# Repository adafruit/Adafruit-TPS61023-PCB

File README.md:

## Adafruit Adafruit MiniBoost 5V at 1A - TPS61023 PCB

<a href="http://www.adafruit.com/products/4654"><br/>
Click here to purchase one from the Adafruit shop</a>

PCB files for the Adafruit Adafruit MiniBoost 5V at 1A - TPS61023.

Format is EagleCAD schematic and board layout
* https://www.adafruit.com/product/4654

### Description

This adorable little board will come in very handy whenever you need a good amount of 5V power. It's the size of a linear regulator, but it's actually a mini-booster! Input 2-5VDC on one side, and get 5V at up to 1A supply on the other. Perfect for use with battery-powered projects with 2 or 3 Alkaline, or a single Lithium battery.

This booster uses a very small but thermally efficient chip from TI, the TPS61023. This chip has nearly everything integrated, including dual 3A MOSFET switches. Note that the switch doesn't tell you the max output, see the tables below for that!

We set the feedback resistors to give a 5.2V output, this is a little higher than 5V which helps account for voltage drop over cables. We took some measurements of the input/output current and max draw using a bench-top power supply and electronic load:

    At 2V DC in, max current out at 5V is 300mA (the minimum input voltage that will 'boot' the booster)
    At 2.5V DC in, max current out at 5V is 500mA (two NiMH rechargables)
    At 3V DC in, max current out at 5V is 800mA (two alkalines or a near-dead LiPo)
    At 3.5V DC in, max current out at 5V is 1100 mA (this is a LiPoly nominal voltage)
    At 4V DC in, max current out at 5V is 1400 mA (3 NiMH, or a fresh LiPoly)

Most people will want to use a Lipoly or LiIon battery with a booster, with a nominal voltage of 3.7V. Here's the efficiencies at that voltage:

    5.2V 100mA out requires 160mA in at 3.7V (88%)
    5.2V 250mA out requires 400mA in at 3.7V (88%)
    5.2V 500mA out requires 800mA in at 3.7V (88%)
    5.2V 1000mA out requires 1800mA in at 3.7V (78%)

As you can see, you'll be humming at ~88% as 'lower' currents of about 500mA and less. You can get 1A out but your efficiency will drop a bit to ~78%

You get one fully assembled breakout with a TPS61023 and components, and a small bit of header. Give it 3-5V on the IN and ground pins. Then you'll have 5V on the OUT pin. The enable pin can be pulled low to disable the output, its a 'true disconnect' so the output will be completely de-powered.

### License

Adafruit invests time and resources providing this open source design, please support Adafruit and open-source hardware by purchasing products from [Adafruit](https://www.adafruit.com)!

Designed by Limor Fried/Ladyada for Adafruit Industries.

Creative Commons Attribution/Share-Alike, all text above must be included in any redistribution.
See license.txt for additional details.

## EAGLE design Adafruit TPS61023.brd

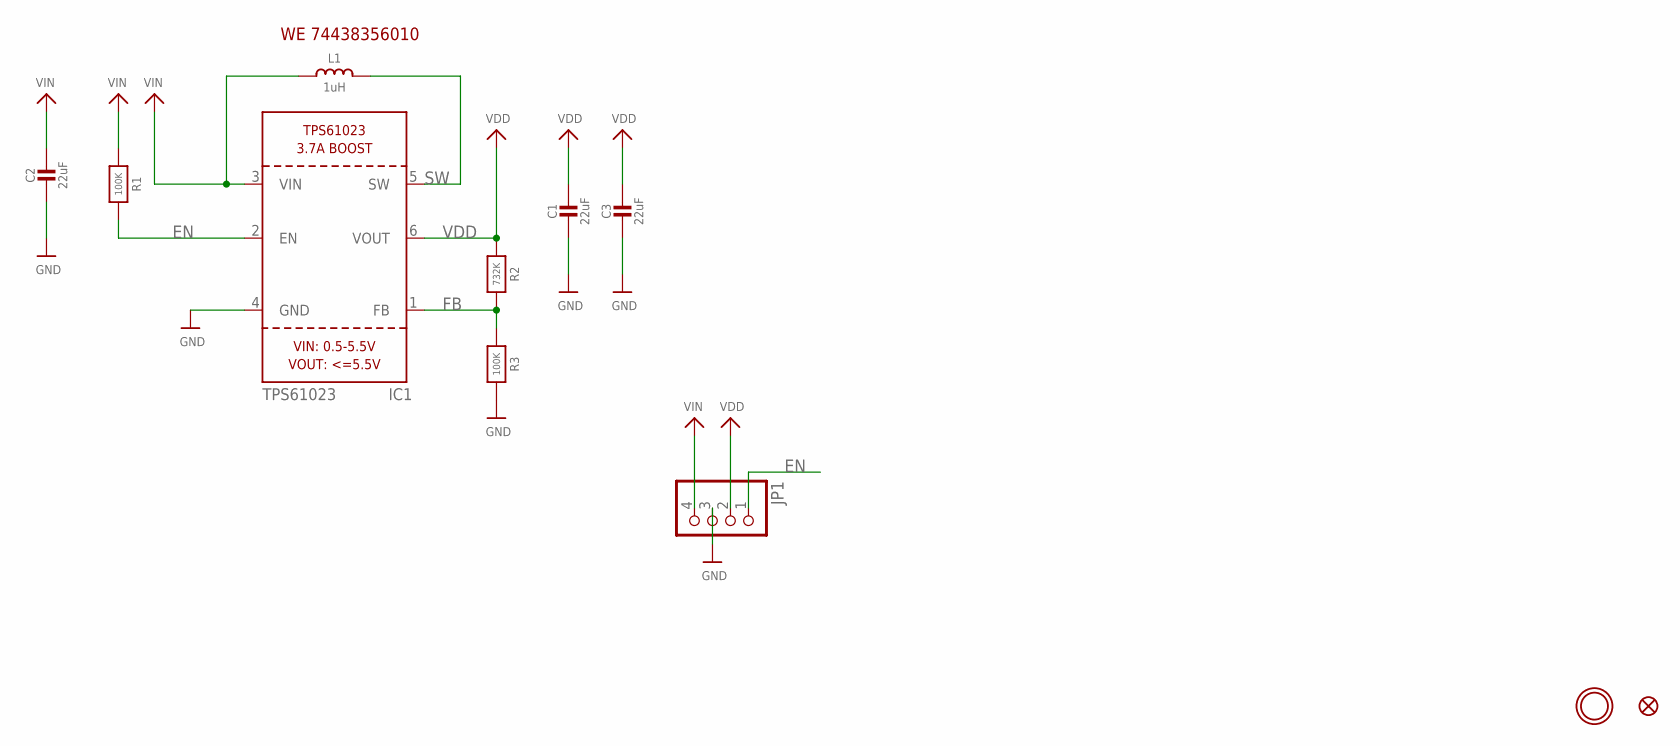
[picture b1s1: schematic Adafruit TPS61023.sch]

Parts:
C1, C2, C3: 22uF; 0805-NO
FID1: FIDUCIAL_1MM
IC1: TPS61023; SOT563
JP1: HEADER-1X4ROUND; 1X04_ROUND
L1: 1uH; INDUCTOR_5X5MM_TDK_VLC5045
R1, R3: 100K; 0603-NO
R2: 732K; 0603-NO
U$9: MOUNTINGHOLE2.5; MOUNTINGHOLE_2.5_PLATED

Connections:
EN: IC1.2 (EN), JP1.1, R1.2
FB: IC1.1 (FB), R2.2, R3.1
GND: C1.2, C2.2, C3.2, IC1.4 (GND), JP1.3, R3.2
SW: IC1.5 (SW), L1.P$2 (2)
VDD: C1.1, C3.1, IC1.6 (VOUT), JP1.2, R2.1
VIN: C2.1, IC1.3 (VIN), JP1.4, L1.P$1 (1), R1.1

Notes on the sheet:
WE 74438356010

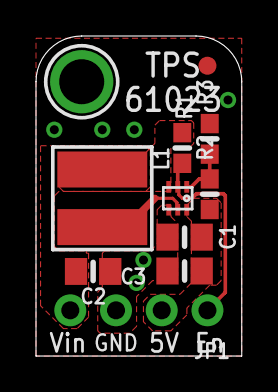
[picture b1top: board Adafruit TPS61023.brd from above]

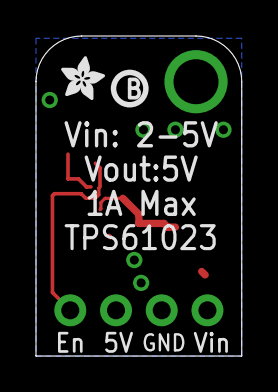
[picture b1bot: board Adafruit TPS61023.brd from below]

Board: 2 copper layers, 11.4 x 17.8 mm, 13 parts (2 on the bottom side), 6 nets.

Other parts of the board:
U$10: PCBFEAT-REV-040
U$11: ADAFRUIT_2.5MM

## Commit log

2020-07-01 Adding board files.

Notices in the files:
parts and their libraries:
microbuilder: This work is placed in the public domain, and may be freely used for commercial and non-commercial work with the following conditions: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
